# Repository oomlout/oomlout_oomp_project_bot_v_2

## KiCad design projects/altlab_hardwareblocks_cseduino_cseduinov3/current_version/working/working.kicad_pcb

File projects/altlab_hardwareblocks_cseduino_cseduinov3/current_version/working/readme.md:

# hardwareblocks_cseduino
 
## summary 
* id: altlab_hardwareblocks_cseduino_cseduinov3
* user: altlab
* name: hardwareblocks_cseduino
* board: cseduinov3
* repo: https://github.com/altLab/HardwareBlocks_CSEduino
* src_file_repo_kicad_pcb: boards/1-layer/cseduinov3.kicad_pcb
* src_file_repo_kicad_pcb_link: https://github.com/altLab/HardwareBlocks_CSEduino/tree/master/boards/1-layer/cseduinov3.kicad_pcb

* src_file_repo_sch: boards/1-layer/cseduinov3.sch
* src_file_repo_sch_link: https://github.com/altLab/HardwareBlocks_CSEduino/tree/master/boards/1-layer/cseduinov3.sch
* full details link: https://github.com/oomlout/oomlout_oomp_project_bot_v_2/tree/main/projects/altlab_hardwareblocks_cseduino_cseduinov3/current_version/working  

## schematic  
  
[schematic (pdf)](working_schematic.pdf) 

## pcb  

[board (pdf)](working.pdf)  

## working_bom
| Id | Designator | Footprint | Quantity | Designation | Supplier and ref |  | None | 
| --- | --- | --- | --- | --- | --- | --- | --- | 
| 1 | C1,C2 | C_Radial_D6.3_L11.2_P2.5 | 2 | 100uF |  |  | [''] | 
| 2 | C3,C4 | C1 | 2 | 22pF |  |  | [''] | 
| 3 | C5 | C2 | 1 | 100nF |  |  | [''] | 
| 4 | D2 | LED-3MM | 1 | LED |  |  | [''] | 
| 5 | IC1 | DIP-28__300_ELL | 1 | ATMEGA328-P |  |  | [''] | 
| 6 | P1 | Pin_Header_Straight_1x02 | 1 | CONN_01X02 |  |  | [''] | 
| 7 | P2 | Pin_Header_Straight_1x14 | 1 | CONN_01X14 |  |  | [''] | 
| 8 | P3 | Pin_Header_Straight_1x04 | 1 | CONN_01X04 |  |  | [''] | 
| 9 | P4 | Pin_Header_Straight_1x08 | 1 | CONN_01X08 |  |  | [''] | 
| 10 | P5 | Pin_Header_Straight_1x06 | 1 | CONN_01X06 |  |  | [''] | 
| 11 | R1 | Resistor_Horizontal_RM10mm | 1 | 470 |  |  | [''] | 
| 12 | R2 | Resistor_Horizontal_RM10mm | 1 | 10K |  |  | [''] | 
| 13 | SW1 | SW_PUSH_SMALL | 1 | SPST |  |  | [''] | 
| 14 | U1 | LM78XX | 1 | 7805 |  |  | [''] | 
| 15 | X1 | Crystal_HC50-U_Vertical | 1 | CRYSTAL |  |  | [''] | 
| 16 | D1 | Diode_DO-41_SOD81_Horizontal_RM10 | 1 | 1N4001 |  |  | [''] | 
| 17 | REF** | Pin_Header_Straight_1x05 | 1 | VCC |  |  | [''] | 
| 18 | REF** | WireConnection_0-8mmDrill | 1 |  ------ |  |  | [''] | 
| 19 | REF** | Pin_Header_Straight_1x05 | 1 | GND |  |  | [''] | 

## bom_schematic
no data

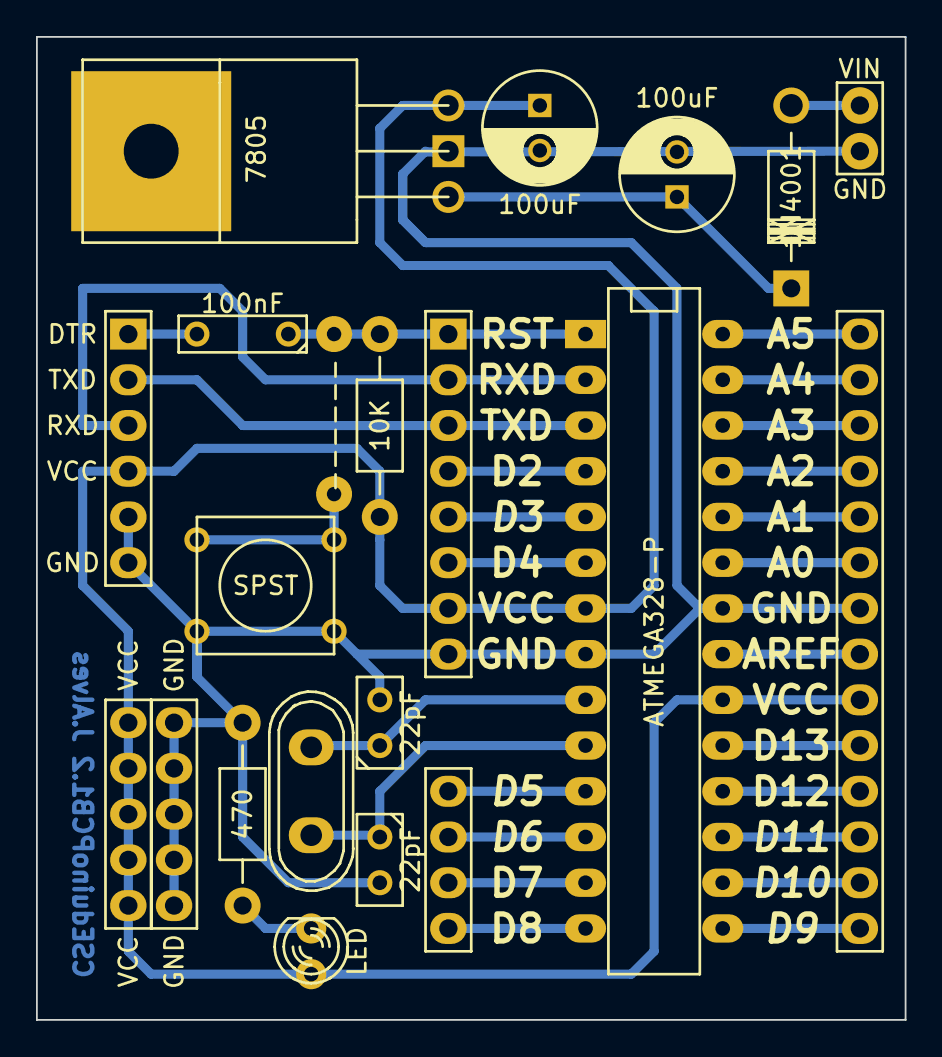
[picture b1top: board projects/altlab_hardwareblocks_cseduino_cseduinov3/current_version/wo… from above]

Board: 2 copper layers, 48.3 x 54.6 mm, 18 parts (0 on the bottom side), 30 nets.

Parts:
C1, C2: 100uF; C_Radial_D6.3_L11.2_P2.5
C3, C4: 22pF; C1
C5: 100nF; C2
D1: 1N4001; Diode_DO-41_SOD81_Horizontal_RM10
D2: LED; LED-3MM
IC1: ATMEGA328-P; DIP-28__300_ELL
P1: CONN_01X02; Pin_Header_Straight_1x02
P2: CONN_01X14; Pin_Header_Straight_1x14
P3: CONN_01X04; Pin_Header_Straight_1x04
P4: CONN_01X08; Pin_Header_Straight_1x08
P5: CONN_01X06; Pin_Header_Straight_1x06
R1: 470; Resistor_Horizontal_RM10mm
R2: 10K; Resistor_Horizontal_RM10mm
SW1: SPST; SW_PUSH_SMALL
U1: 7805; LM78XX
X1: CRYSTAL; Crystal_HC50-U_Vertical

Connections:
+5V: C2.1, D2.1, IC1.7, IC1.20, P2.6, P4.7, P5.4, R2.1, U1.VO
GND: C1.2, C2.2, C3.2, C4.2, IC1.8, IC1.22, P1.2, P2.8, P4.8, P5.5, P5.6, R1.2, SW1.2, U1.GND
unnamed: C1.1, D1.2, U1.VI
unnamed: C3.1, IC1.10, X1.1
unnamed: C4.1, IC1.9, X1.2
unnamed: C5.1, IC1.1, P4.1, R2.2, SW1.1
unnamed: C5.2, P5.1
unnamed: D1.1, P1.1
unnamed: D2.2, R1.1
unnamed: IC1.2, P4.2, P5.3
unnamed: IC1.3, P4.3, P5.2
unnamed: IC1.4, P4.4
unnamed: IC1.5, P4.5
unnamed: IC1.6, P4.6
unnamed: IC1.11, P3.1
unnamed: IC1.12, P3.2
unnamed: IC1.13, P3.3
unnamed: IC1.14, P3.4
unnamed: IC1.15, P2.1
unnamed: IC1.16, P2.2
unnamed: IC1.17, P2.3
unnamed: IC1.18, P2.4
unnamed: IC1.19, P2.5
unnamed: IC1.21, P2.7
unnamed: IC1.23, P2.9
unnamed: IC1.24, P2.10
unnamed: IC1.25, P2.11
unnamed: IC1.26, P2.12
unnamed: IC1.27, P2.13
unnamed: IC1.28, P2.14

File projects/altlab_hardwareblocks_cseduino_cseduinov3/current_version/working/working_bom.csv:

"Id";"Designator";"Footprint";"Quantity";"Designation";"Supplier and ref";
1;"C1,C2";"C_Radial_D6.3_L11.2_P2.5";2;"100uF";;;
2;"C3,C4";"C1";2;"22pF";;;
3;"C5";"C2";1;"100nF";;;
4;"D2";"LED-3MM";1;"LED";;;
5;"IC1";"DIP-28__300_ELL";1;"ATMEGA328-P";;;
6;"P1";"Pin_Header_Straight_1x02";1;"CONN_01X02";;;
7;"P2";"Pin_Header_Straight_1x14";1;"CONN_01X14";;;
8;"P3";"Pin_Header_Straight_1x04";1;"CONN_01X04";;;
9;"P4";"Pin_Header_Straight_1x08";1;"CONN_01X08";;;
10;"P5";"Pin_Header_Straight_1x06";1;"CONN_01X06";;;
11;"R1";"Resistor_Horizontal_RM10mm";1;"470";;;
12;"R2";"Resistor_Horizontal_RM10mm";1;"10K";;;
13;"SW1";"SW_PUSH_SMALL";1;"SPST";;;
14;"U1";"LM78XX";1;"7805";;;
15;"X1";"Crystal_HC50-U_Vertical";1;"CRYSTAL";;;
16;"D1";"Diode_DO-41_SOD81_Horizontal_RM10";1;"1N4001";;;
17;"REF**";"Pin_Header_Straight_1x05";1;"VCC";;;
18;"REF**";"WireConnection_0-8mmDrill";1;" ------";;;
19;"REF**";"Pin_Header_Straight_1x05";1;"GND";;;

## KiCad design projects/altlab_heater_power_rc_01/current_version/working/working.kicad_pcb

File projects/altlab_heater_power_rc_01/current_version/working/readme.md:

# heater
 
## summary 
* id: altlab_heater_power_rc_01
* user: altlab
* name: heater
* board: power_rc_01
* repo: https://github.com/altLab/heater
* src_file_repo_kicad_pcb: power_rc_01.kicad_pcb
* src_file_repo_kicad_pcb_link: https://github.com/altLab/heater/tree/main/power_rc_01.kicad_pcb

* src_file_repo_sch: power_rc_01.sch
* src_file_repo_sch_link: https://github.com/altLab/heater/tree/main/power_rc_01.sch
* full details link: https://github.com/oomlout/oomlout_oomp_project_bot_v_2/tree/main/projects/altlab_heater_power_rc_01/current_version/working  

## schematic  
  
[schematic (pdf)](working_schematic.pdf) 

## pcb  

[board (pdf)](working.pdf)  

## working_bom
| Id | Designator | Footprint | Quantity | Designation | Supplier and ref |  | None | 
| --- | --- | --- | --- | --- | --- | --- | --- | 
| 1 | T1 | Transformer_37x44 | 1 | Transformer_1P_1S |  |  | [''] | 
| 2 | C1,C2,C3 | CP_Radial_D5.0mm_P2.50mm | 3 | CP1 |  |  | [''] | 
| 3 | D1 | Diode_Bridge_15.7x15.7x6.3mm_P10.8mm | 1 | D_Bridge_-A+A |  |  | [''] | 
| 4 | D2,D3,D4 | LED_D3.0mm_Horizontal_O3.81mm_Z10.0mm | 3 | LED |  |  | [''] | 
| 5 | D5 | TO-218-3_Horizontal_TabUp | 1 | Q_TRIAC_A1A2G |  |  | [''] | 
| 6 | R1,R3,R4,R5,R6 | R_Axial_DIN0309_L9.0mm_D3.2mm_P2.54mm_Vertical | 5 | R |  |  | [''] | 
| 7 | R7 | JST_EH_B2B-EH-A_1x02_P2.50mm_Vertical | 1 | Heater |  |  | [''] | 
| 8 | SW1 | SW_PUSH_6mm | 1 | SW_Push |  |  | [''] | 
| 9 | U1 | 3-SIP_Module_V7805-1000 | 1 | V7805-1000 |  |  | [''] | 
| 10 | U2 | DIP-6_W7.62mm | 1 | MOC3021 |  |  | [''] | 
| 11 | U3 | DIP-8_W7.62mm | 1 | ATTINY85-20PU |  |  | [''] | 
| 12 | LOGO*** | ALTLAB_LOGO | 1 | ALTLAB |  |  | [''] | 
| 13 | F1 | Fuseholder_Cylinder-5x20mm_Schurter_0031_8201_Horizontal_Open | 1 | DFP10112 |  |  | [''] | 

## bom_schematic
| Ref | Qnty | Value | Cmp name | Footprint | Description | Vendor | DNP | 
| --- | --- | --- | --- | --- | --- | --- | --- | 
| C1, C2, C3 | 3 | CP1 | CP1-Device | Capacitor_THT:CP_Radial_D5.0mm_P2.50mm |  |  |  | 
| D1 | 1 | D_Bridge_-A+A | D_Bridge_-A+A | Diode_THT:Diode_Bridge_15.7x15.7x6.3mm_P10.8mm | Diode bridge, -ve/AC/+ve/AC |  |  | 
| D2, D3, D4 | 3 | LED | LED | LED_THT:LED_D3.0mm_Horizontal_O3.81mm_Z10.0mm | Light emitting diode |  |  | 
| D5 | 1 | Q_TRIAC_A1A2G | Q_TRIAC_A1A2G | Package_TO_SOT_THT:TO-218-3_Horizontal_TabUp | Triode for alternating current, anode1/anode2/gate |  |  | 
| F1 | 1 | DFP10112 | DFP10112-dk_Thermal-Cutoffs-Thermal-Fuses | Fuse:Fuseholder_Cylinder-5x20mm_Schurter_0031_8201_Horizontal_Open |  |  |  | 
| J1 | 1 | Conn_WallSocket | Conn_WallSocket | Connector_Wire:SolderWirePad_1x02_P7.62mm_Drill2mm | 3-pin german wall socket, no Earth wire (110VAC, 220VAC) |  |  | 
| R1, R3, R4, R5, R6 | 5 | R | R | Resistor_THT:R_Axial_DIN0309_L9.0mm_D3.2mm_P2.54mm_Vertical | Resistor |  |  | 
| R7 | 1 | Heater | Heater | Connector_JST:JST_EH_B2B-EH-A_1x02_P2.50mm_Vertical | Resistive heater |  |  | 
| SW1 | 1 | SW_Push | SW_Push | Button_Switch_THT:SW_PUSH_6mm | Push button switch, generic, two pins |  |  | 
| T1 | 1 | Transformer_1P_1S | Transformer_1P_1S | Transformer_THT:Transformer_37x44 | Transformer, single primary, single secondary |  |  | 
| U1 | 1 | V7805-1000 | V7805-1000-dk_DC-DC-Converters | digikey-footprints:3-SIP_Module_V7805-1000 |  |  |  | 
| U2 | 1 | MOC3021 | MOC3021-dk_Optoisolators-Triac-SCR-Output | digikey-footprints:DIP-6_W7.62mm |  |  |  | 
| U3 | 1 | ATTINY85-20PU | ATTINY85-20PU-dk_Embedded-Microcontrollers | digikey-footprints:DIP-8_W7.62mm |  |  |  |

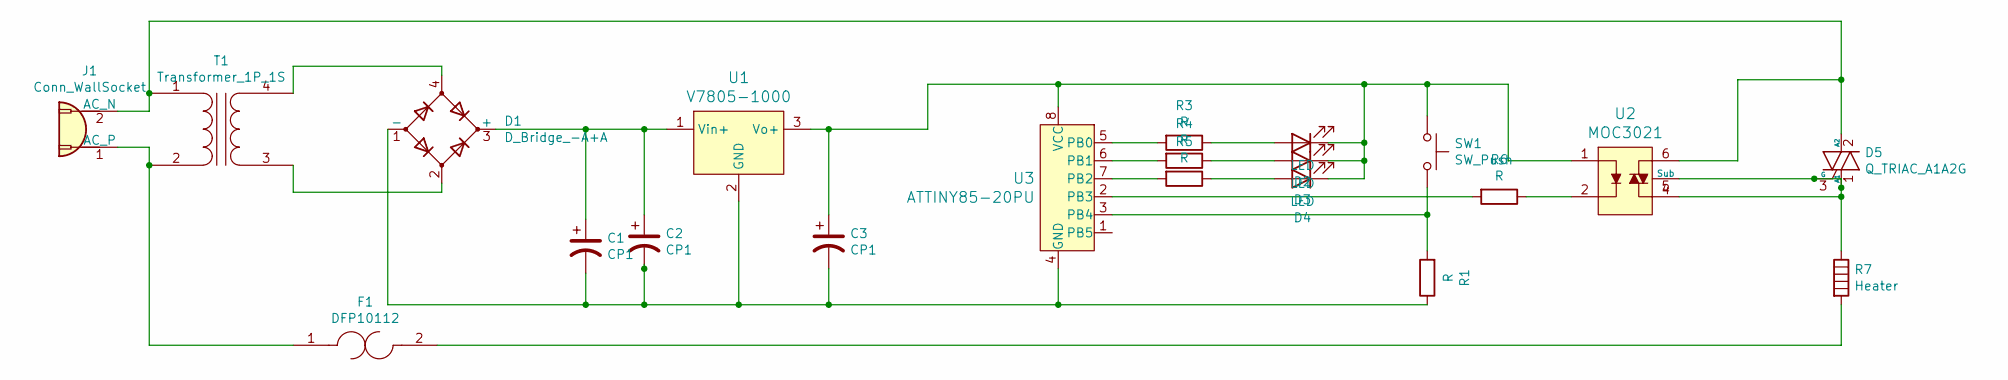
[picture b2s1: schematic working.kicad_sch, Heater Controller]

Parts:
C1, C2, C3: CP1; CP_Radial_D5.0mm_P2.50mm
D1: D_Bridge_-A+A; Diode_Bridge_15.7x15.7x6.3mm_P10.8mm
D2, D3, D4: LED; LED_D3.0mm_Horizontal_O3.81mm_Z10.0mm
D5: Q_TRIAC_A1A2G; TO-218-3_Horizontal_TabUp
F1: DFP10112; Fuseholder_Cylinder-5x20mm_Schurter_0031_8201_Horizontal_Op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; MPN DFP10112; Digi-Key_PN 285-1901-ND
J1: Conn_WallSocket; SolderWirePad_1x02_P7.62mm_Drill2mm
R1, R3, R4, R5, R6: R; R_Axial_DIN0309_L9.0mm_D3.2mm_P2.54mm_Vertical
R7: Heater; JST_EH_B2B-EH-A_1x02_P2.50mm_Vertical
SW1: SW_Push; SW_PUSH_6mm
T1: Transformer_1P_1S; Transformer_37x44
U1: V7805-1000; 3-SIP_Module_V7805-1000; MPN V7805-1000; Digi-Key_PN 102-1715-ND
U2: MOC3021; DIP-6_W7.62mm; MPN MOC3021; Digi-Key_PN 160-1374-5-ND
U3: ATTINY85-20PU; DIP-8_W7.62mm; MPN ATTINY85-20PU; Digi-Key_PN ATTINY85-20PU-ND

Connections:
unnamed: C1.1, C2.1, D1.3 (+), U1.1 (Vin+)
unnamed: C1.2, C2.2, C3.2, D1.1 (-), R1.1, U1.2 (GND), U3.4 (GND)
unnamed: C3.1, D2.1 (K), D3.1 (K), D4.1 (K), SW1.1, U1.3 (Vo+), U2.1, U3.8 (VCC)
unnamed: D1.2, T1.3 (SA)
unnamed: D1.4, T1.4 (SB)
unnamed: D2.2 (A), R3.1
unnamed: D3.2 (A), R4.1
unnamed: D4.2 (A), R5.1
unnamed: D5.1 (A1), D5.3 (G), R7.1, U2.4, U2.5 (Sub)
unnamed: D5.2 (A2), J1.2 (AC_N), T1.1 (AA), U2.6
unnamed: F1.1, J1.1 (AC_P), T1.2 (AB)
unnamed: F1.2, R7.2
unnamed: R1.2, SW1.2, U3.3 (PB4)
unnamed: R3.2, U3.5 (PB0)
unnamed: R4.2, U3.6 (PB1)
unnamed: R5.2, U3.7 (PB2)
unnamed: R6.1, U2.2
unnamed: R6.2, U3.2 (PB3)

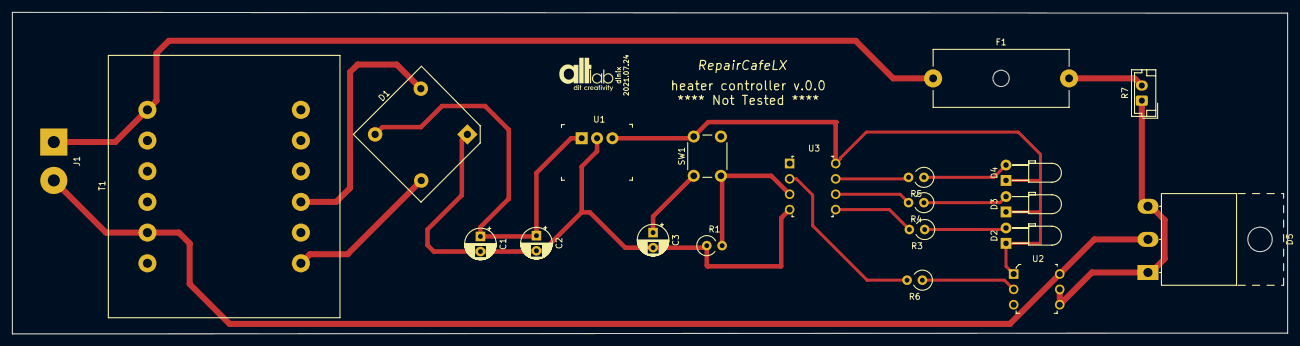
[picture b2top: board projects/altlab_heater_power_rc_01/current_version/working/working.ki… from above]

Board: 2 copper layers, 211.1 x 53.2 mm, 22 parts (0 on the bottom side), 18 nets.

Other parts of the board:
LOGO***: ALTLAB; ALTLAB_LOGO

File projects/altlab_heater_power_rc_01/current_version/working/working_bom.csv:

"Id";"Designator";"Footprint";"Quantity";"Designation";"Supplier and ref";
1;"T1";"Transformer_37x44";1;"Transformer_1P_1S";;;
2;"C1,C2,C3";"CP_Radial_D5.0mm_P2.50mm";3;"CP1";;;
3;"D1";"Diode_Bridge_15.7x15.7x6.3mm_P10.8mm";1;"D_Bridge_-A+A";;;
4;"D2,D3,D4";"LED_D3.0mm_Horizontal_O3.81mm_Z10.0mm";3;"LED";;;
5;"D5";"TO-218-3_Horizontal_TabUp";1;"Q_TRIAC_A1A2G";;;
6;"R1,R3,R4,R5,R6";"R_Axial_DIN0309_L9.0mm_D3.2mm_P2.54mm_Vertical";5;"R";;;
7;"R7";"JST_EH_B2B-EH-A_1x02_P2.50mm_Vertical";1;"Heater";;;
8;"SW1";"SW_PUSH_6mm";1;"SW_Push";;;
9;"U1";"3-SIP_Module_V7805-1000";1;"V7805-1000";;;
10;"U2";"DIP-6_W7.62mm";1;"MOC3021";;;
11;"U3";"DIP-8_W7.62mm";1;"ATTINY85-20PU";;;
12;"LOGO***";"ALTLAB_LOGO";1;"ALTLAB";;;
13;"F1";"Fuseholder_Cylinder-5x20mm_Schurter_0031_8201_Horizontal_Open";1;"DFP10112";;;

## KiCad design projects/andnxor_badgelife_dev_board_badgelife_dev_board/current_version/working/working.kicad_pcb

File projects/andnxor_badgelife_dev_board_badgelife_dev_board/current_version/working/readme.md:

# badgelife_dev_board
 
## summary 
* id: andnxor_badgelife_dev_board_badgelife_dev_board
* user: andnxor
* name: badgelife_dev_board
* board: badgelife_dev_board
* repo: https://github.com/ANDnXOR/badgelife_dev_board
* src_file_repo_kicad_pcb: badgelife_dev_board.kicad_pcb
* src_file_repo_kicad_pcb_link: https://github.com/ANDnXOR/badgelife_dev_board/tree/master/badgelife_dev_board.kicad_pcb

* src_file_repo_sch: badgelife_dev_board.sch
* src_file_repo_sch_link: https://github.com/ANDnXOR/badgelife_dev_board/tree/master/badgelife_dev_board.sch
* full details link: https://github.com/oomlout/oomlout_oomp_project_bot_v_2/tree/main/projects/andnxor_badgelife_dev_board_badgelife_dev_board/current_version/working  

## schematic  
  
[schematic (pdf)](working_schematic.pdf) 

## pcb  

[board (pdf)](working.pdf)  

## working_bom
| Id | Designator | Footprint | Quantity | Designation | Supplier and ref |  | None | 
| --- | --- | --- | --- | --- | --- | --- | --- | 
| 1 | REF**,REF**,REF**,REF** | Pin_Header_Straight_2x09_Pitch2.54mm-NoSilk | 4 | Pin_Header_Straight_2x09_Pitch2.54mm |  |  | [''] | 
| 2 | X1 | Badgelife-Shitty-2x2 | 1 | Badgelife_shitty_connector |  |  | [''] | 
| 3 | J1,J2 | Power_Rail-01x08 | 2 | Conn_01x08 |  |  | [''] | 
| 4 | J3,J4 | Power_Rail-01x09 | 2 | Conn_01x09 |  |  | [''] | 
| 5 | G*** | badgelife-shitty-label-3.3v | 1 | LOGO |  |  | [''] | 
| 6 | G*** | badgelife-shitty-label-sda | 1 | LOGO |  |  | [''] | 
| 7 | G*** | badgelife-shitty-label-scl | 1 | LOGO |  |  | [''] | 
| 8 | G*** | badgelife-shitty-label-gnd | 1 | LOGO |  |  | [''] | 
| 9 | G*** | badgelife-shitty-devboard-silk | 1 | LOGO |  |  | [''] | 

## bom_schematic
| Ref | Qnty | Value | Cmp name | Footprint | Description | Vendor | DNP | 
| --- | --- | --- | --- | --- | --- | --- | --- | 
| J1, J2 | 2 | Conn_01x08 | Conn_01x08 |  |  |  |  | 
| J3, J4 | 2 | Conn_01x09 | Conn_01x09 |  |  |  |  | 
| X1 | 1 | Badgelife_shitty_connector | Badgelife_shitty_connector | mrmeeseeks:Badgelife-Shitty-2x2 |  |  |  |

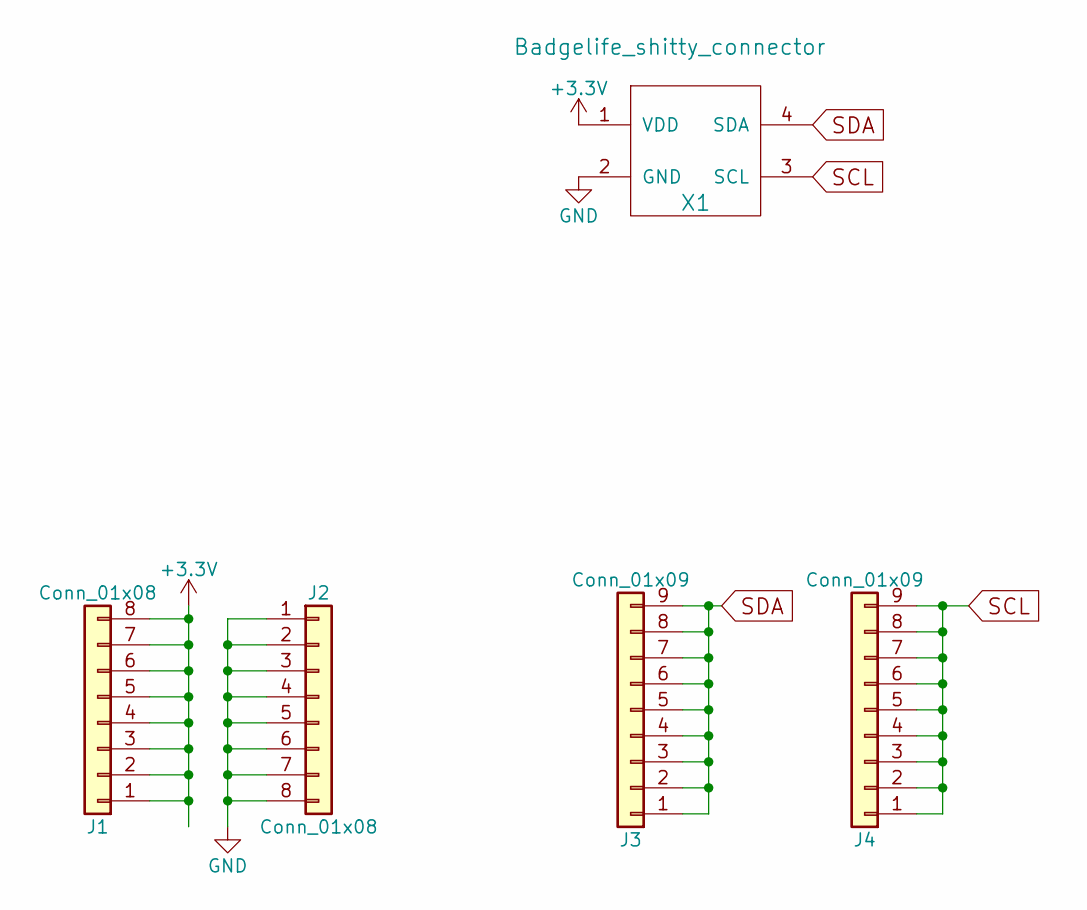
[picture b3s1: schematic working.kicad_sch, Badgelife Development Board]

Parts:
J1, J2: Conn_01x08
J3, J4: Conn_01x09
X1: Badgelife_shitty_connector; Badgelife-Shitty-2x2

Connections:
+3V3: J1.1, J1.2, J1.3, J1.4, J1.5, J1.6, J1.7, J1.8, X1.1 (VDD)
GND: J2.1, J2.2, J2.3, J2.4, J2.5, J2.6, J2.7, J2.8, X1.2 (GND)
SCL: J4.1, J4.2, J4.3, J4.4, J4.5, J4.6, J4.7, J4.8, J4.9, X1.3 (SCL)
SDA: J3.1, J3.2, J3.3, J3.4, J3.5, J3.6, J3.7, J3.8, J3.9, X1.4 (SDA)

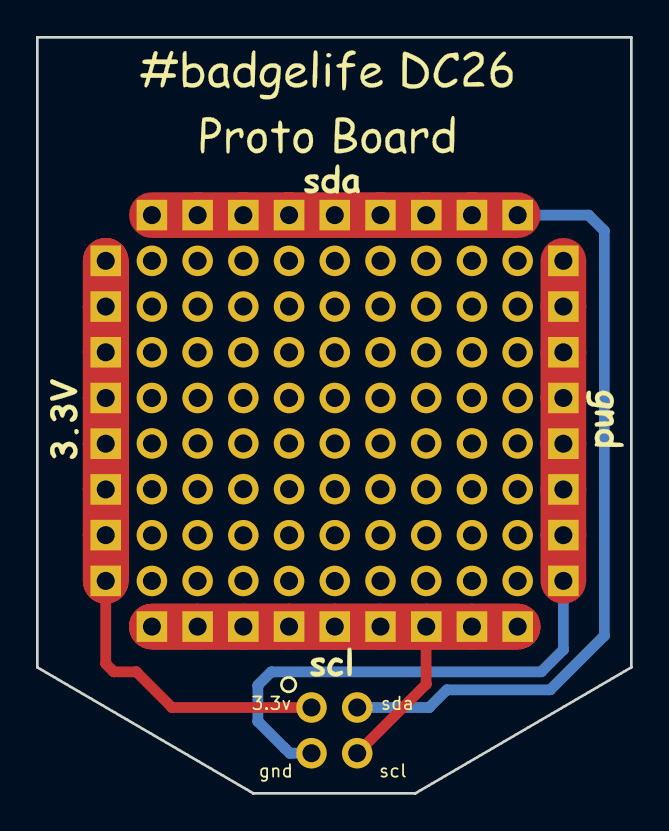
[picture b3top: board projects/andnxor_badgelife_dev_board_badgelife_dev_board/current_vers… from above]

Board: 2 copper layers, 33.0 x 42.0 mm, 5 parts (0 on the bottom side), 4 nets.

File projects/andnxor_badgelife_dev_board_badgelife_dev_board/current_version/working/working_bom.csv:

"Id";"Designator";"Footprint";"Quantity";"Designation";"Supplier and ref";
1;"REF**,REF**,REF**,REF**";"Pin_Header_Straight_2x09_Pitch2.54mm-NoSilk";4;"Pin_Header_Straight_2x09_Pitch2.54mm";;;
2;"X1";"Badgelife-Shitty-2x2";1;"Badgelife_shitty_connector";;;
3;"J1,J2";"Power_Rail-01x08";2;"Conn_01x08";;;
4;"J3,J4";"Power_Rail-01x09";2;"Conn_01x09";;;
5;"G***";"badgelife-shitty-label-3.3v";1;"LOGO";;;
6;"G***";"badgelife-shitty-label-sda";1;"LOGO";;;
7;"G***";"badgelife-shitty-label-scl";1;"LOGO";;;
8;"G***";"badgelife-shitty-label-gnd";1;"LOGO";;;
9;"G***";"badgelife-shitty-devboard-silk";1;"LOGO";;;

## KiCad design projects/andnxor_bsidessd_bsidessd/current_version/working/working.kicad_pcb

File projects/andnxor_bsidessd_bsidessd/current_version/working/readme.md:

# bsidessd
 
## summary 
* id: andnxor_bsidessd_bsidessd
* user: andnxor
* name: bsidessd
* board: bsidessd
* repo: https://github.com/ANDnXOR/BSidesSD
* src_file_repo_kicad_pcb: bsidessd/bsidessd.kicad_pcb
* src_file_repo_kicad_pcb_link: https://github.com/ANDnXOR/BSidesSD/tree/master/bsidessd/bsidessd.kicad_pcb

* src_file_repo_sch: bsidessd/bsidessd.sch
* src_file_repo_sch_link: https://github.com/ANDnXOR/BSidesSD/tree/master/bsidessd/bsidessd.sch
* full details link: https://github.com/oomlout/oomlout_oomp_project_bot_v_2/tree/main/projects/andnxor_bsidessd_bsidessd/current_version/working  

## schematic  
  
[schematic (pdf)](working_schematic.pdf) 

## pcb  

[board (pdf)](working.pdf)  

## working_bom
| Id | Designator | Footprint | Quantity | Designation | Supplier and ref |  | None | 
| --- | --- | --- | --- | --- | --- | --- | --- | 
| 1 | C1,C2 | C_0805_2012Metric | 2 | 1uF |  |  | [''] | 
| 2 | C3,C5 | C_0805_2012Metric | 2 | 10uF |  |  | [''] | 
| 3 | C4 | C_0805_2012Metric | 1 | 1nF |  |  | [''] | 
| 4 | D1,D4 | D_SOD-323 | 2 | D_Schottky |  |  | [''] | 
| 5 | D2 | LED_0603_1608Metric | 1 | RED |  |  | [''] | 
| 6 | D3,D5,D7,D8,D9 | LED_WS2812B_PLCC4_5.0x5.0mm_P3.2mm | 5 | WS2812B |  |  | [''] | 
| 7 | D6 | LED_0603_1608Metric | 1 | GREEN |  |  | [''] | 
| 8 | J1,J2 | PinHeader_1x05_P2.54mm_Vertical | 2 | Conn_01x05 |  |  | [''] | 
| 9 | J3 | USB_Micro-B_Amphenol_10103594-0001LF_Horizontal | 1 | USB_B_Micro |  |  | [''] | 
| 10 | R1 | R_0805_2012Metric | 1 | 1.5K |  |  | [''] | 
| 11 | TP1 | PinHeader_1x01_P2.54mm_Vertical | 1 | SWD |  |  | [''] | 
| 12 | TP2 | PinHeader_1x01_P2.54mm_Vertical | 1 | SWC |  |  | [''] | 
| 13 | TP3 | PinHeader_1x01_P2.54mm_Vertical | 1 | Battery |  |  | [''] | 
| 14 | TP4 | PinHeader_1x01_P2.54mm_Vertical | 1 | Ground |  |  | [''] | 
| 15 | U1 | TQFP-32_7x7mm_P0.8mm | 1 | ATSAMD21E18A-AUT |  |  | [''] | 
| 16 | U2 | SOT-23-5 | 1 | AP2112K-3.3 |  |  | [''] | 
| 17 | SW1 | SW_SPST_PTS810 | 1 | PTS810 |  |  | [''] | 
| 18 | R2 | R_0805_2012Metric | 1 | 10K |  |  | [''] | 

## bom_schematic
| Ref | Qnty | Value | Cmp name | Footprint | Description | Vendor | DNP | 
| --- | --- | --- | --- | --- | --- | --- | --- | 
| BT1, BT2, BT3 | 3 | AAA | Battery |  | Multiple-cell battery |  |  | 
| C1, C2 | 2 | 1uF | C_Small | Capacitor_SMD:C_0805_2012Metric | Unpolarized capacitor, small symbol |  |  | 
| C3, C5 | 2 | 10uF | C_Small | Capacitor_SMD:C_0805_2012Metric | Unpolarized capacitor, small symbol |  |  | 
| C4 | 1 | 1nF | C_Small | Capacitor_SMD:C_0805_2012Metric | Unpolarized capacitor, small symbol |  |  | 
| D1, D4 | 2 | D_Schottky | D_Schottky | Diode_SMD:D_SOD-323 | Schottky diode |  |  | 
| D2 | 1 | RED | LED | LED_SMD:LED_0603_1608Metric | Light emitting diode |  |  | 
| D3, D5, D7, D8, D9 | 5 | WS2812B | WS2812B | LED_SMD:LED_WS2812B_PLCC4_5.0x5.0mm_P3.2mm | RGB LED with integrated controller |  |  | 
| D6 | 1 | GREEN | LED | LED_SMD:LED_0603_1608Metric | Light emitting diode |  |  | 
| J1, J2 | 2 | Conn_01x05 | Conn_01x05 | Connector_PinHeader_2.54mm:PinHeader_1x05_P2.54mm_Vertical | Generic connector, single row, 01x05, script generated (kicad-library-utils/schlib/autogen/connector/) |  |  | 
| J3 | 1 | USB_B_Micro | USB_B_Micro-Connector | Connector_USB:USB_Micro-B_Amphenol_10103594-0001LF_Horizontal |  |  |  | 
| R1 | 1 | 1.5K | R_US | Resistor_SMD:R_0805_2012Metric | Resistor, US symbol |  |  | 
| R2 | 1 | 10K | R_US | Resistor_SMD:R_0805_2012Metric | Resistor, US symbol |  |  | 
| SW1 | 1 | PTS810 | PTS810-pts810_alt | Button_Switch_SMD:SW_SPST_PTS810 |  |  |  | 
| TP1 | 1 | SWD | TestPoint | Connector_PinHeader_2.54mm:PinHeader_1x01_P2.54mm_Vertical | test point |  |  | 
| TP2 | 1 | SWC | TestPoint | Connector_PinHeader_2.54mm:PinHeader_1x01_P2.54mm_Vertical | test point |  |  | 
| TP3 | 1 | Battery | TestPoint | Connector_PinHeader_2.54mm:PinHeader_1x01_P2.54mm_Vertical | test point |  |  | 
| TP4 | 1 | Ground | TestPoint | Connector_PinHeader_2.54mm:PinHeader_1x01_P2.54mm_Vertical | test point |  |  | 
| U1 | 1 | ATSAMD21E18A-AUT | ATSAMD21E18A-AUT-ATSAMD21E | Package_QFP:TQFP-32_7x7mm_P0.8mm |  |  |  | 
| U2 | 1 | AP2112K-3.3 | AP2112K-3.3-Regulator_Linear | Package_TO_SOT_SMD:SOT-23-5 |  |  |  |

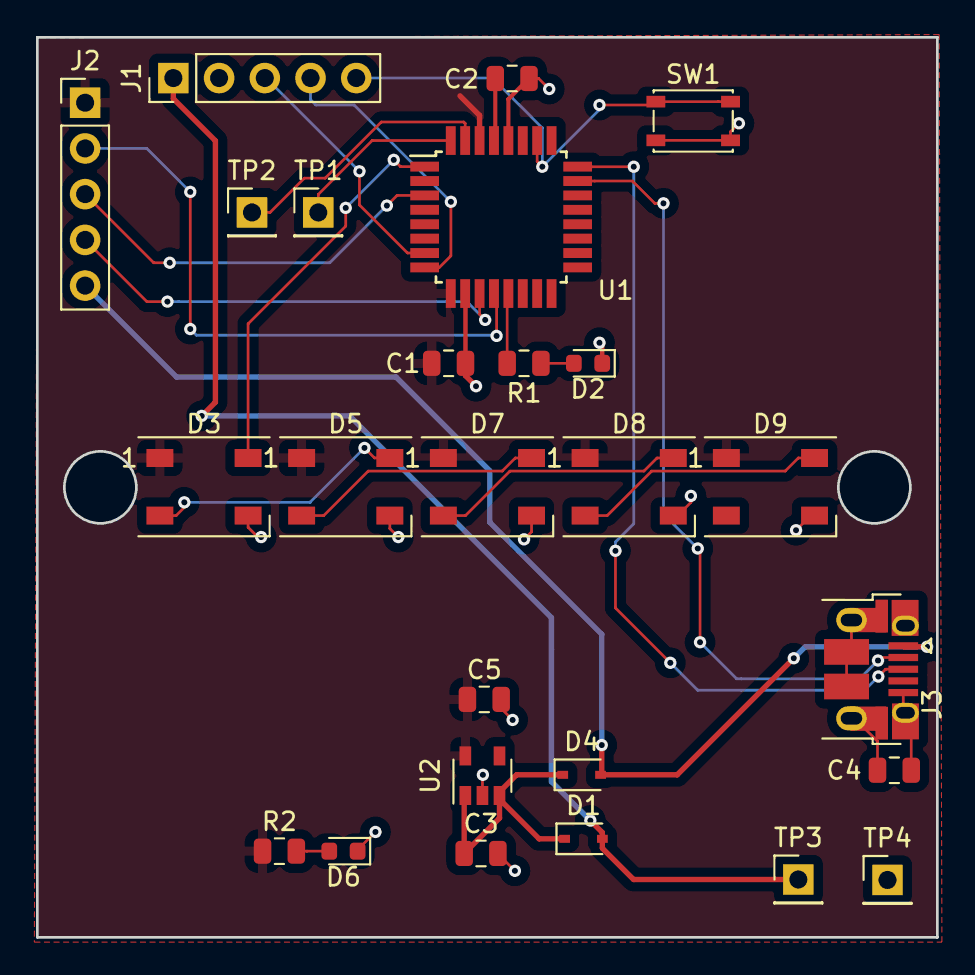
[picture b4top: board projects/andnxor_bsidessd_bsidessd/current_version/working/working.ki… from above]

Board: 2 copper layers, 50.0 x 50.0 mm, 26 parts (0 on the bottom side), 24 nets.

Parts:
C1, C2: 1uF; C_0805_2012Metric
C3, C5: 10uF; C_0805_2012Metric
C4: 1nF; C_0805_2012Metric
D1, D4: D_Schottky; D_SOD-323
D2: RED; LED_0603_1608Metric
D3, D5, D7, D8, D9: WS2812B; LED_WS2812B_PLCC4_5.0x5.0mm_P3.2mm
D6: GREEN; LED_0603_1608Metric
J1, J2: Conn_01x05; PinHeader_1x05_P2.54mm_Vertical
J3: USB_B_Micro; USB_Micro-B_Amphenol_10103594-0001LF_Horizontal
R1: 1.5K; R_0805_2012Metric
R2: 10K; R_0805_2012Metric
SW1: PTS810; SW_SPST_PTS810
TP1: SWD; PinHeader_1x01_P2.54mm_Vertical
TP2: SWC; PinHeader_1x01_P2.54mm_Vertical
TP3: Battery; PinHeader_1x01_P2.54mm_Vertical
TP4: Ground; PinHeader_1x01_P2.54mm_Vertical
U1: ATSAMD21E18A-AUT; TQFP-32_7x7mm_P0.8mm
U2: AP2112K-3.3; SOT-23-5

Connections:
+3V3: C1.1, C5.1, D3.1, D5.1, D7.1, D8.1, D9.1, J2.1, R2.1, U1.9, U1.30, U2.5
/D0_A4_PAU08_SDA: J2.4, U1.11
/D1_A0_PAU02: J2.3, U1.3
/D2_A1_PAU09_SCL_MISO: J2.2, U1.12
/D3_A3_PAU07_RXD_SCK: J1.4, U1.8
/D4_A2_PAU06_TXD_MOSI: J1.3, U1.7
/D+: J3.3, U1.24
/D-: J3.2, U1.23
/LED: D3.4, U1.1
/~RESET: J1.5, SW1.1, U1.26
GND: C1.2, C2.2, C3.2, C4.1, C4.2, C5.2, D2.1, D3.3, D5.3, D6.1, D7.3, D8.3, D9.3, J1.2, J3.5, J3.6, SW1.2, TP4.1, U1.10, U1.28, U2.2
unnamed: C2.1, U1.29
unnamed: C3.1, D1.1, D4.1, U2.1, U2.3
unnamed: D2.2, R1.1
unnamed: D3.2, D5.4
unnamed: D5.2, D7.4
unnamed: D6.2, R2.2
unnamed: D7.2, D8.4
unnamed: D8.2, D9.4
unnamed: R1.2, U1.13
unnamed: TP1.1, U1.32
unnamed: TP2.1, U1.31
VBAT: D1.2, J1.1, TP3.1
VBUS: D4.2, J2.5, J3.1

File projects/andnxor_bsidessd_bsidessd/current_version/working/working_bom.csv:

"Id";"Designator";"Footprint";"Quantity";"Designation";"Supplier and ref";
1;"C1,C2";"C_0805_2012Metric";2;"1uF";;;
2;"C3,C5";"C_0805_2012Metric";2;"10uF";;;
3;"C4";"C_0805_2012Metric";1;"1nF";;;
4;"D1,D4";"D_SOD-323";2;"D_Schottky";;;
5;"D2";"LED_0603_1608Metric";1;"RED";;;
6;"D3,D5,D7,D8,D9";"LED_WS2812B_PLCC4_5.0x5.0mm_P3.2mm";5;"WS2812B";;;
7;"D6";"LED_0603_1608Metric";1;"GREEN";;;
8;"J1,J2";"PinHeader_1x05_P2.54mm_Vertical";2;"Conn_01x05";;;
9;"J3";"USB_Micro-B_Amphenol_10103594-0001LF_Horizontal";1;"USB_B_Micro";;;
10;"R1";"R_0805_2012Metric";1;"1.5K";;;
11;"TP1";"PinHeader_1x01_P2.54mm_Vertical";1;"SWD";;;
12;"TP2";"PinHeader_1x01_P2.54mm_Vertical";1;"SWC";;;
13;"TP3";"PinHeader_1x01_P2.54mm_Vertical";1;"Battery";;;
14;"TP4";"PinHeader_1x01_P2.54mm_Vertical";1;"Ground";;;
15;"U1";"TQFP-32_7x7mm_P0.8mm";1;"ATSAMD21E18A-AUT";;;
16;"U2";"SOT-23-5";1;"AP2112K-3.3";;;
17;"SW1";"SW_SPST_PTS810";1;"PTS810";;;
18;"R2";"R_0805_2012Metric";1;"10K";;;

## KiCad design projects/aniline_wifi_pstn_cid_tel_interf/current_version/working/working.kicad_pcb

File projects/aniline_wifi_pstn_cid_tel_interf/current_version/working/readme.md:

# wifi_pstn_cid
 
## summary 
* id: aniline_wifi_pstn_cid_tel_interf
* user: aniline
* name: wifi_pstn_cid
* board: tel_interf
* repo: https://github.com/aniline/wifi_pstn_cid
* src_file_repo_kicad_pcb: tel_interf.kicad_pcb
* src_file_repo_kicad_pcb_link: https://github.com/aniline/wifi_pstn_cid/tree/master/tel_interf.kicad_pcb

* src_file_repo_sch: tel_interf.sch
* src_file_repo_sch_link: https://github.com/aniline/wifi_pstn_cid/tree/master/tel_interf.sch
* full details link: https://github.com/oomlout/oomlout_oomp_project_bot_v_2/tree/main/projects/aniline_wifi_pstn_cid_tel_interf/current_version/working  

## schematic  
  
[schematic (pdf)](working_schematic.pdf) 

## pcb  

[board (pdf)](working.pdf)  

## working_bom
| Id | Designator | Footprint | Quantity | Designation | Supplier and ref |  | None | 
| --- | --- | --- | --- | --- | --- | --- | --- | 
| 1 | C1 | C_Disc_D12_P7.75 | 1 | 33nF, 150V |  |  | [''] | 
| 2 | C2 | C_Disc_D12_P7.75 | 1 | 33nF, 150v |  |  | [''] | 
| 3 | C3 | C_Rect_L18_W6_P15 | 1 | 100nF, 250V |  |  | [''] | 
| 4 | CON1 | Pin_Header_Straight_2x03 | 1 | AVR-ISP-6 |  |  | [''] | 
| 5 | D1 | WOM_BRIDGE | 1 | W10M |  |  | [''] | 
| 6 | D2,D3 | Diode_DO-41_SOD81_Horizontal_RM10 | 2 | ZENER 8.2V |  |  | [''] | 
| 7 | D5,D6 | Diode_DO-41_SOD81_Horizontal_RM10 | 2 | ZENER 3.3V |  |  | [''] | 
| 8 | D7 | Diode_DO-41_SOD81_Horizontal_RM10 | 1 | 3.3v |  |  | [''] | 
| 9 | IC1 | DIP-6_W7.62mm | 1 | 4N35 |  |  | [''] | 
| 10 | IC2 | DIP-8_W7.62mm | 1 | HT9032D |  |  | [''] | 
| 11 | IC3 | DIP-14_W7.62mm | 1 | ATTINY84-P |  |  | [''] | 
| 12 | J1,J2 | RJ11_PTH_6P4C_STAG | 2 | RJ11_PTH_STAGGER |  |  | [''] | 
| 13 | P1 | USB_Micro-B | 1 | USB_OTG |  |  | [''] | 
| 14 | RV1 | Potentiometer_Triwood_RM-065 | 1 | 10K |  |  | [''] | 
| 15 | SW1 | SW_PUSH_SMALL | 1 | ESP_REST |  |  | [''] | 
| 16 | SW2 | SW_PUSH_SMALL | 1 | AVR_REST |  |  | [''] | 
| 17 | SW3 | SW_PUSH_SMALL | 1 | PROG |  |  | [''] | 
| 18 | T1 | TRANSFO-AUDIO-EL14 | 1 | 600E 1:1 |  |  | [''] | 
| 19 | U1 | SOT-223 | 1 | LD1117S33TR |  |  | [''] | 
| 20 | U2 | DIP-8_W7.62mm | 1 | LM393 |  |  | [''] | 
| 21 | U3 | ESP-12 | 1 | ESP-12 |  |  | [''] | 
| 22 | Y1 | Crystal_HC49-U_Vertical | 1 | 3.579545Mhz |  |  | [''] | 
| 23 | Y2 | Crystal_HC49-U_Vertical | 1 | 8 Mhz |  |  | [''] | 
| 24 | C4,C7 | c_elec_5x5.3 | 2 | 10uF |  |  | [''] | 
| 25 | C10,C11,C14,C15 | C_0805_HandSoldering | 4 | 22pF |  |  | [''] | 
| 26 | R10,R11,R12,R13 | R_1206_HandSoldering | 4 | 1K |  |  | [''] | 
| 27 | R3,R4,R2 | R_1206_HandSoldering | 3 | 220K |  |  | [''] | 
| 28 | C5,C6 | C_Disc_D7.5_P5 | 2 | 47nF |  |  | [''] | 
| 29 | D8 | LED-1206 | 1 | LED |  |  | [''] | 
| 30 | D4 | Diode_DO-35_SOD27_Horizontal_RM10 | 1 | 1N4148 |  |  | [''] | 
| 31 | C8 | TantalC_SizeA_EIA-3216_HandSoldering | 1 | 1uF |  |  | [''] | 
| 32 | JP1 | Pin_Header_Straight_1x03 | 1 | RX sel. |  |  | [''] | 
| 33 | P2 | Pin_Header_Straight_1x03 | 1 | ESP_UART |  |  | [''] | 
| 34 | C9,C12,C13 | C_0805_HandSoldering | 3 | 0.1uF |  |  | [''] | 
| 35 | R1,R6 | R_1206_HandSoldering | 2 | 100K |  |  | [''] | 
| 36 | R5 | R_1206_HandSoldering | 1 | 10K |  |  | [''] | 
| 37 | R7,R8 | R_1206_HandSoldering | 2 | 4.7K |  |  | [''] | 
| 38 | R9 | R_1206_HandSoldering | 1 | 1k |  |  | [''] | 

## bom_schematic
no data

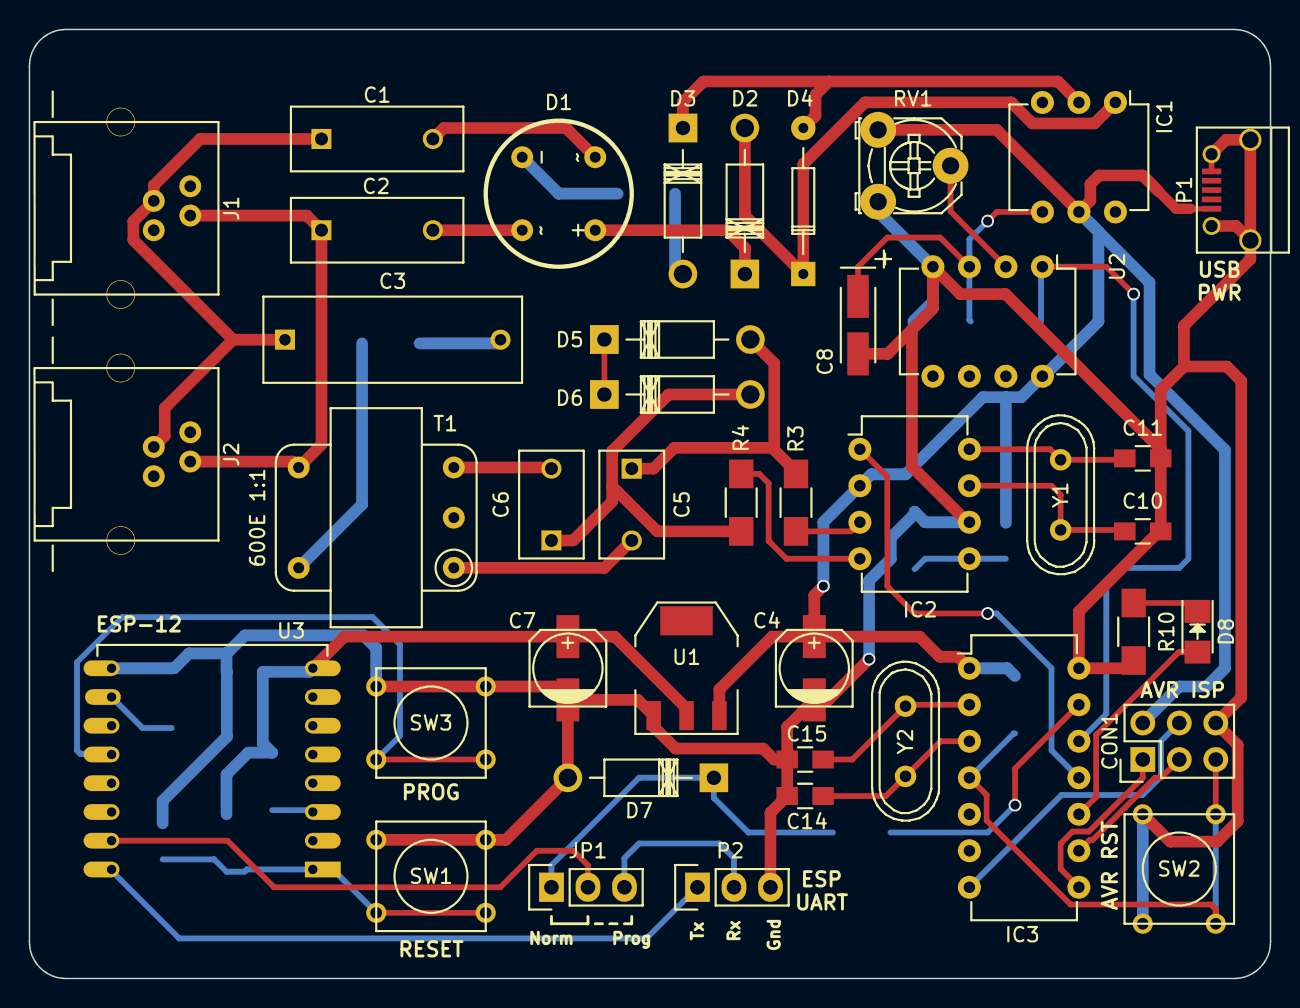
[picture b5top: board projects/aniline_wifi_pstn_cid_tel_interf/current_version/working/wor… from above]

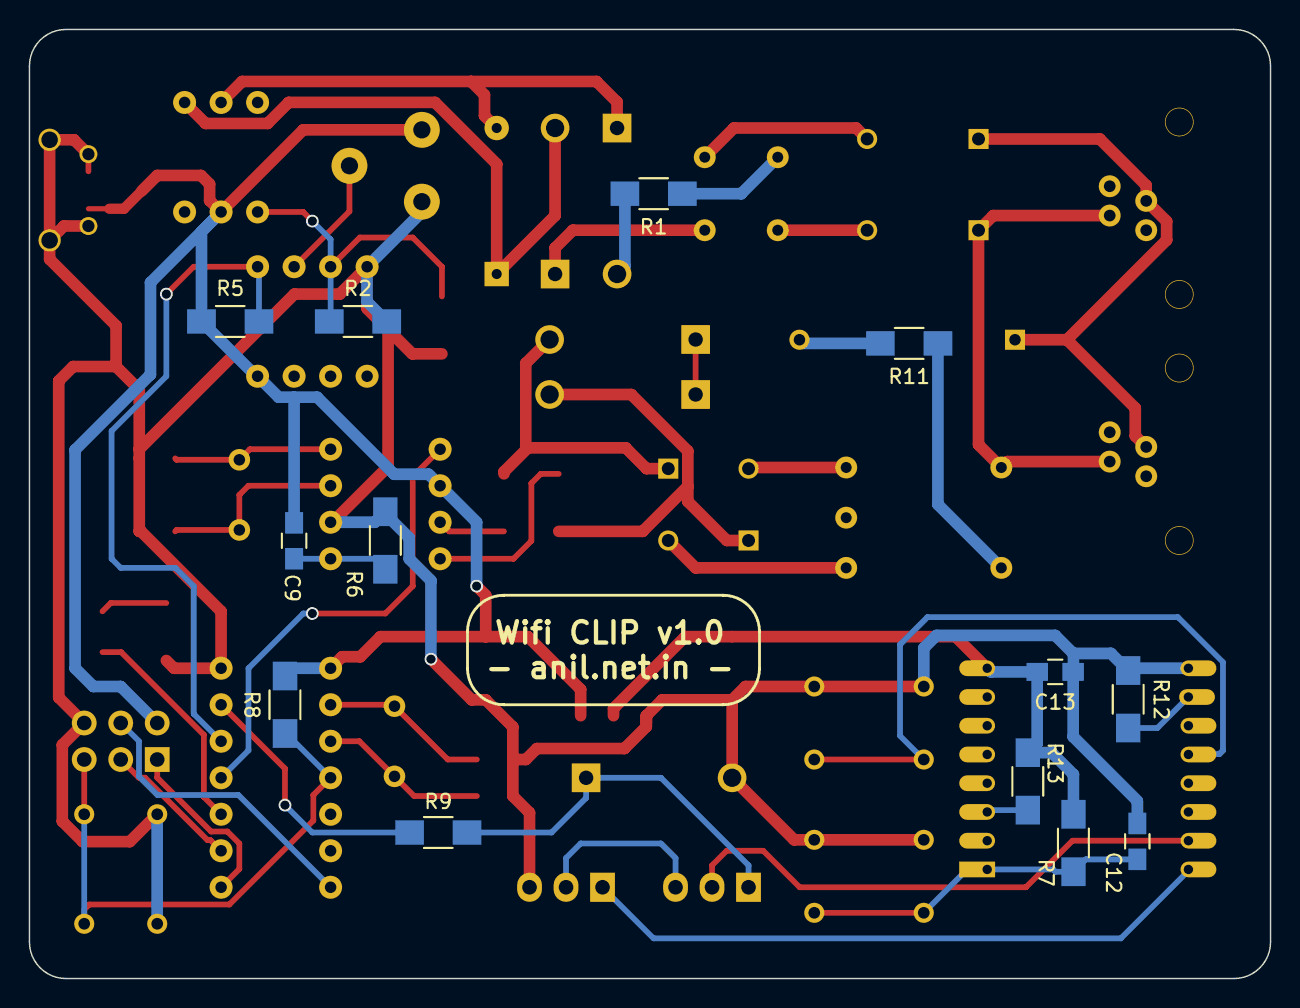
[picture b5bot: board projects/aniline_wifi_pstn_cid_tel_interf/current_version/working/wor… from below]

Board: 2 copper layers, 86.4 x 66.0 mm, 55 parts (13 on the bottom side), 45 nets.

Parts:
C1: 33nF, 150V; C_Disc_D12_P7.75
C2: 33nF, 150v; C_Disc_D12_P7.75
C3: 100nF, 250V; C_Rect_L18_W6_P15
C4, C7: 10uF; c_elec_5x5.3
C5, C6: 47nF; C_Disc_D7.5_P5
C8: 1uF; TantalC_SizeA_EIA-3216_HandSoldering
C9, C12, C13: 0.1uF; C_0805_HandSoldering
C10, C11, C14, C15: 22pF; C_0805_HandSoldering
CON1: AVR-ISP-6; Pin_Header_Straight_2x03
D1: W10M; WOM_BRIDGE
D2, D3: ZENER 8.2V; Diode_DO-41_SOD81_Horizontal_RM10
D4: 1N4148; Diode_DO-35_SOD27_Horizontal_RM10
D5, D6: ZENER 3.3V; Diode_DO-41_SOD81_Horizontal_RM10
D7: 3.3v; Diode_DO-41_SOD81_Horizontal_RM10
D8: LED; LED-1206
IC1: 4N35; DIP-6_W7.62mm
IC2: HT9032D; DIP-8_W7.62mm
IC3: ATTINY84-P; DIP-14_W7.62mm
J1, J2: RJ11_PTH_STAGGER; RJ11_PTH_6P4C_STAG
JP1: RX sel.; Pin_Header_Straight_1x03
P1: USB_OTG; USB_Micro-B
P2: ESP_UART; Pin_Header_Straight_1x03
R1, R6: 100K; R_1206_HandSoldering
R2, R3, R4: 220K; R_1206_HandSoldering
R5: 10K; R_1206_HandSoldering
R7, R8: 4.7K; R_1206_HandSoldering
R9: 1k; R_1206_HandSoldering
R10, R11, R12, R13: 1K; R_1206_HandSoldering
RV1: 10K; Potentiometer_Triwood_RM-065
SW1: ESP_REST; SW_PUSH_SMALL
SW2: AVR_REST; SW_PUSH_SMALL
SW3: PROG; SW_PUSH_SMALL
T1: 600E 1:1; TRANSFO-AUDIO-EL14
U1: LD1117S33TR; SOT-223
U2: LM393; DIP-8_W7.62mm
U3: ESP-12
Y1: 3.579545Mhz; Crystal_HC49-U_Vertical
Y2: 8 Mhz; Crystal_HC49-U_Vertical

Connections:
+3V3: C7.1, C13.2, R7.1, R13.1, U1.2, U3.8
+5V: C4.1, C9.1, CON1.2, IC1.5, IC2.2, IC3.1, P1.1, R5.1, R8.2, RV1.1, U1.3, U2.8
AVR_MISO: CON1.1, IC3.8
AVR_MOSI: CON1.4, IC3.7
AVR_REST: CON1.5, IC3.4, R8.1, SW2.2
AVR_SCL: CON1.3, IC3.9
CLIP: IC2.1, IC3.11
GND: C4.2, C7.2, C8.2, C10.2, C11.2, C12.2, C13.1, C14.2, C15.2, CON1.6, D7.2, IC2.6, IC3.14, P1.5, P1.6, P2.3, R2.2, R6.2, R10.2, R12.1, RV1.3, SW1.1, SW2.1, SW3.1, U1.1, U2.4, U3.9
NUMOUT: IC3.13, R9.1
unnamed: C1.2, D1.4
unnamed: C2.2, D1.2
unnamed: C3.2, R11.2
unnamed: C5.1, D5.2, R3.1
unnamed: C5.2, T1.1
unnamed: C6.1, D6.2, R4.1
unnamed: C6.2, T1.3
unnamed: C8.1, IC1.4, R2.1, U2.3
unnamed: C9.2, IC2.5, R6.1
unnamed: C10.1, IC2.7, Y1.1
unnamed: C11.1, IC2.8, Y1.2
unnamed: C12.1, R7.2, SW1.2, U3.1
unnamed: C14.1, IC3.3, Y2.1
unnamed: C15.1, IC3.2, Y2.2
unnamed: D1.1, D2.1
unnamed: D1.3, R1.1
unnamed: D2.2, D4.1, IC1.1
unnamed: D3.1, D4.2, IC1.2
unnamed: D3.2, R1.2
unnamed: D5.1, D6.1
unnamed: D7.1, JP1.1, R9.2
unnamed: D8.1, R10.1
unnamed: D8.2, IC3.10
unnamed: IC2.3, R3.2
unnamed: IC2.4, R4.2
unnamed: JP1.2, U3.15
unnamed: JP1.3, P2.2
unnamed: P2.1, U3.16
unnamed: R11.1, T1.5
unnamed: R12.2, U3.10
unnamed: R13.2, U3.3
unnamed: RV1.2, U2.2
unnamed: SW3.2, U3.12
RING: IC3.12, R5.2, U2.1
TEL1: C1.1, C3.1, J1.2, J2.2
TEL2: C2.1, J1.3, J2.3, T1.4

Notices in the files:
projects/andnxor_badgelife_dev_board_badgelife_dev_board/current_version/working/working.kicad_sch:
Apache 2.0 License
